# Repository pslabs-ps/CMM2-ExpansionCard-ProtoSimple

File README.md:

# CMM2-ExpansionCard-ProtoSimple

This is simple prototyping card with various signals exposed.

Kicad project can be downloaded here:

[Kicad prototyping card](Kicad/proto_vard_simple/)

Expansion system and cards can be purchased here: [PS Labs](https://sklep.pslabs.pl/Maximite-c91)

# WARNING!

Expansion card have to have edges chamfered, using unchamfered card will result in slot damage.

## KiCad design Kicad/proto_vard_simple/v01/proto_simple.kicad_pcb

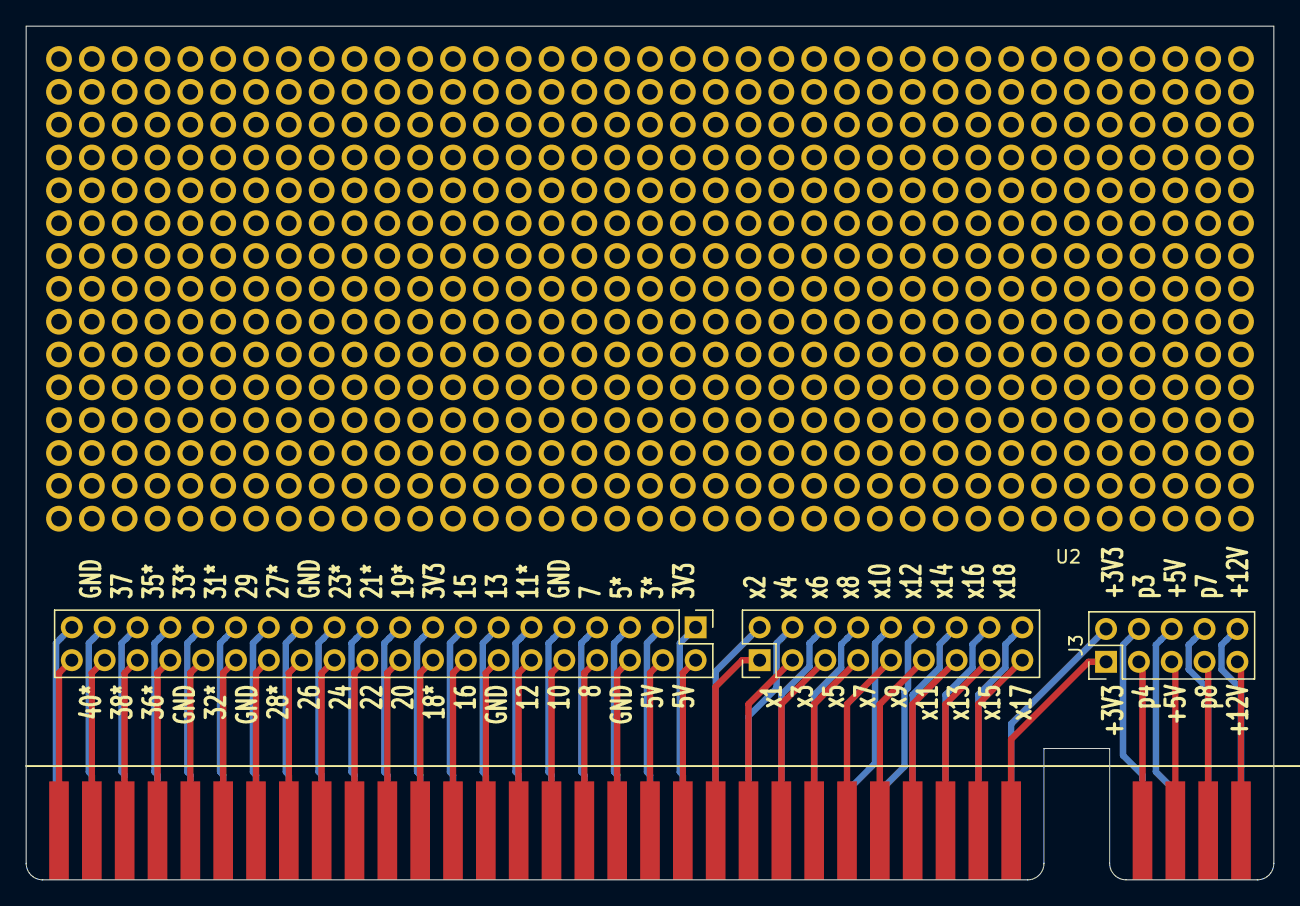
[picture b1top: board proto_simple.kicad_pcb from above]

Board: 2 copper layers, 96.5 x 66.0 mm, 5 parts (0 on the bottom side), 68 nets.

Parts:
J1: Conn_02x20_Odd_Even; Pin_Header_Straight_2x20_Pitch2.54mm
J2: Conn_02x09_Odd_Even; Pin_Header_Straight_2x09_Pitch2.54mm
J3: Conn_02x05_Odd_Even; Pin_Header_Straight_2x05_Pitch2.54mm
U1: maxim_exp_slot; maxim_exp_card_narrow
U2: breadboard; breadboard_m2_small

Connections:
/1: J1.1, U1.1
/2: J1.2, U1.2
/3: J1.3, U1.3
/4: J1.4, U1.4
/5: J1.5, U1.5
/6: J1.6, U1.6
/7: J1.7, U1.7
/8: J1.8, U1.8
/9: J1.9, U1.9
/10: J1.10, U1.10
/11: J1.11, U1.11
/12: J1.12, U1.12
/13: J1.13, U1.13
/14: J1.14, U1.14
/15: J1.15, U1.15
/16: J1.16, U1.16
/17: J1.17, U1.17
/18: J1.18, U1.18
/19: J1.19, U1.19
/20: J1.20, U1.20
/21: J1.21, U1.21
/22: J1.22, U1.22
/23: J1.23, U1.23
/24: J1.24, U1.24
/25: J1.25, U1.25
/26: J1.26, U1.26
/27: J1.27, U1.27
/28: J1.28, U1.28
/29: J1.29, U1.29
/30: J1.30, U1.30
/31: J1.31, U1.31
/32: J1.32, U1.32
/33: J1.33, U1.33
/34: J1.34, U1.34
/35: J1.35, U1.35
/36: J1.36, U1.36
/37: J1.37, U1.37
/38: J1.38, U1.38
/39: J1.39, U1.39
/40: J1.40, U1.40
/p1: J3.2, U1.p1
/p2: J3.1, U1.p2
/p3: J3.4, U1.p3
/p4: J3.3, U1.p4
/p5: J3.6, U1.p5
/p6: J3.5, U1.p6
/p7: J3.8, U1.p7
/p8: J3.7, U1.p8
/p9: J3.10, U1.p9
/p10: J3.9, U1.p10
/x1: J2.2, U1.x1
/x2: J2.1, U1.x2
/x3: J2.4, U1.x3
/x4: J2.3, U1.x4
/x5: J2.6, U1.x5
/x6: J2.5, U1.x6
/x7: J2.8, U1.x7
/x8: J2.7, U1.x8
/x9: J2.10, U1.x9
/x10: J2.9, U1.x10
/x11: J2.12, U1.x11
/x12: J2.11, U1.x12
/x13: J2.14, U1.x13
/x14: J2.13, U1.x14
/x15: J2.16, U1.x15
/x16: J2.15, U1.x16
/x17: J2.18, U1.x17
/x18: J2.17, U1.x18
